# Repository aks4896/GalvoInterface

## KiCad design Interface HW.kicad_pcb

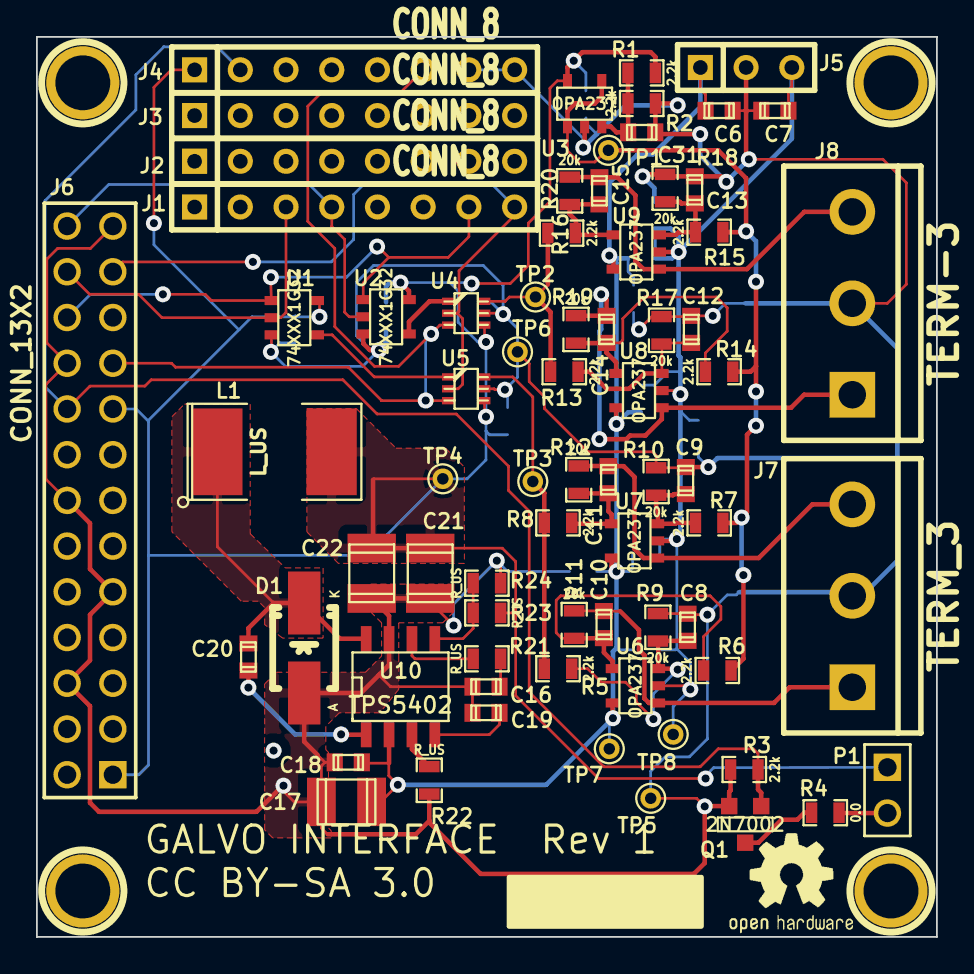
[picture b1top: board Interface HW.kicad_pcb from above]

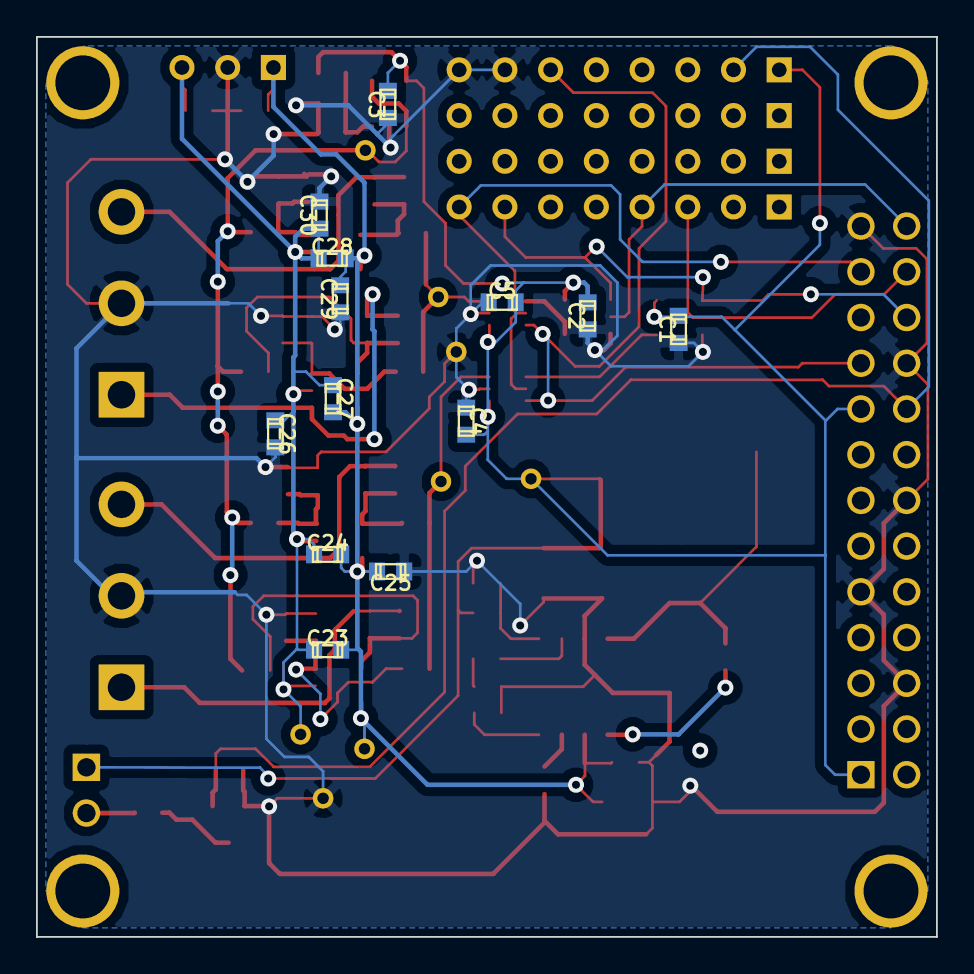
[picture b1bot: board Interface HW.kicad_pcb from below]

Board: 2 copper layers, 50.0 x 50.0 mm, 89 parts (13 on the bottom side), 37 nets.

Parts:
1PIN, 1PIN#2, 1PIN#3, 1PIN#4: P***; 1pin
C1, C2, C3, C4, C5, C6, C7, C23, C24, C25, C26, C27, C28, C29, C30, C31: 0.1uF; c_0603
C8, C9, C10, C11, C12, C13, C14, C15: 4700pF; c_0603
C16, C18, C19, C20: CSMALL; c_0603
C17, C21, C22: 10uF; c_1210
D1: B130; Diode-SMA
J1, J2, J3, J4: CONN_8; SIL-8
J5: TE: 640456-3; SIL-3
J6: CONN_13X2; pin_array_13x2
J7: TERM_3; bornier3
J8: TERM-3; bornier3
L1: L_US; SM2112L
P1: CONNECTOR_2; PIN_ARRAY_2X1
Q1: 2N7002; SOT23GDS
R1, R2, R3, R5, R6, R7, R8, R13, R14, R15, R16: 2.2k; SM0603_Resistor
R4: 0.0; SM0603_Resistor
R9, R10, R11, R12, R17, R18, R19, R20: 20k; SM0603_Resistor
R21, R22, R23, R24: R_US; SM0603_Resistor
TP1, TP2, TP3, TP4, TP5, TP6, TP7, TP8: TEST; PINTST
U1, U2: 74XXX1G32; SOT23-5
U3, U6, U7, U8, U9: OPA237; SOT23-5
U4, U5: DACX311; sc70-6
U10: TPS5402; SO8E

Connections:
3V3: C1.1, C2.1, C3.1, C4.1, C5.1, C21.1, C22.1, J4.1, J6.1, J6.17, L1.2, P1.1, R1.1, R23.1, TP4.1, U1.5, U2.5, U3.5, U4.4, U5.4
+15V: C6.1, C17.1, C18.1, C23.1, C24.1, C25.1, C27.1, C28.1, C29.1, J5.1, TP7.1, U6.5, U7.5, U8.5, U9.5, U10.2
-15V: C7.2, C23.2, C24.2, C26.2, C27.2, C28.2, C30.2, J5.3, TP8.1, U6.2, U7.2, U8.2, U9.2
/Interface HW-01/GPIO_12: J4.2, J6.18, Q1.G, R3.1
/Interface HW-01/SCL_A: J1.3, J6.24, U1.2
/Interface HW-01/SDA_A: J1.4, J6.26, U2.2
/Interface HW-01/SPICLK_A: J1.8, J6.23, U4.2, U5.2
/Interface HW-01/SPISIMO_A: J4.6, J6.19, U4.3, U5.3
/Interface HW-01/SPISTE_A: J1.7, J6.22, U1.1, U2.1
DAC_X: R5.2, R8.2, TP3.1, U5.6
DAC_Y: R13.2, R16.2, TP2.1, U4.6
GND: C1.2, C2.2, C3.2, C4.2, C5.2, C6.2, C7.1, C8.1, C9.1, C12.1, C13.1, C16.2, C17.2, C18.2, C19.2, C21.2, C22.2, C25.2, C26.1, C29.2, C30.1, C31.2, D1.1, J4.7, J4.8, J5.2, J6.6, J6.9, J6.14, J6.20, J6.25, J7.2, J8.2, Q1.S, R2.2, R3.2, R9.2, R10.2, R17.2, R18.2, R22.2, R24.2, TP5.1, TP6.1, U1.3, U2.3, U3.2, U4.5, U5.5, U10.7
unnamed: U1.4, U5.1
unnamed: Q1.D, R4.2
unnamed: P1.2, R4.1
unnamed: U2.4, U4.1
unnamed: C31.1, R1.2, R2.1, U3.3
unnamed: C11.1, J7.3, R12.1, U7.1
unnamed: C9.2, R7.1, R10.1, U7.3
unnamed: C8.2, R5.1, R9.1, U6.3
unnamed: C11.2, R8.1, R12.2, U7.4
unnamed: C10.2, R6.1, R11.2, U6.4
unnamed: C10.1, J7.1, R11.1, U6.1
unnamed: C15.1, J8.3, R20.1, U9.1
unnamed: C13.2, R15.1, R18.1, U9.3
unnamed: C12.2, R13.1, R17.1, U8.3
unnamed: C15.2, R16.1, R20.2, U9.4
unnamed: C14.2, R14.1, R19.2, U8.4
unnamed: C14.1, J8.1, R19.1, U8.1
unnamed: C20.1, U10.1
unnamed: C20.2, D1.2, L1.1, U10.8
unnamed: R23.2, R24.1, U10.5
unnamed: R21.1, U10.6
unnamed: R22.1, U10.3
unnamed: C19.1, U10.4
unnamed: C16.1, R21.2
REF_1.65V: R6.2, R7.2, R14.2, R15.2, TP1.1, U3.1, U3.4

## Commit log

2014-03-11 Added initial files
2014-03-11 Added ref folder and DAC datasheet
2014-03-11 Added schematic and pinout of controlstick
2014-03-11 Completed pinout of controlStick
2014-03-11 Added F2806x datasheet/TRM
2014-03-11 added op-amp datasheet
2014-03-11 Added op-amp, and op-amp datasheet
2014-03-11 Added resistor symbol
2014-03-12 Added diff-amp circuit to schematic
2014-03-21 Added block diagram, modified gitignore to ignore dia temp files
2014-03-26 Added SPI TRM for F28027 (same for F28069), and OR gate datasheet
2014-03-26 Changed analog circuit to be differential output
2014-03-30 commit before attempting to add 2nd and 3rd page
2014-04-01 Intermediate commit so I can split up the schematic
2014-04-01 Working on adding new page, intermediate commit
2014-04-02 Added connector drawing and block diagram png
2014-04-02 Still working
2014-04-02 added new page for Y axis
2014-04-05 Modified schematic, added laser driver and page for buck converter
2014-04-05 Added more refs
2014-04-05 added buck converter datasheet
2014-04-05 Added buck converter to schematic, almost done
2014-04-05 Schematic before assigning ref des and netlisting
2014-04-05 added todo'
2014-04-09 Started layout
2014-04-16 Changed PCB size to 5x5cm, got most components placed
2014-04-16 Added a cap to ref, chages buck converter caps, more routing, didn't pull in netlist
2014-04-16 More routing, added power supply test points, added mounting holes
2014-04-23 no unconnected PINSgit status git status
2014-04-23 Silk cleanup
2014-04-23 Added OSHW logo
2014-07-15 Updated Interface HW PDF
2015-10-20 Updated schematic
2015-10-20 Added README
2015-10-20 Removed unused temp files
2015-10-20 Corrected note about bandwidth of amp circuit
2015-10-20 Added license file
2015-10-21 Created gerber files for release
2015-10-22 2nd try submitting files, board outline added
2015-10-22 Added more autosave files to gitignore

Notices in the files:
Interface HW.kicad_pcb:
CC BY-SA 3.0
